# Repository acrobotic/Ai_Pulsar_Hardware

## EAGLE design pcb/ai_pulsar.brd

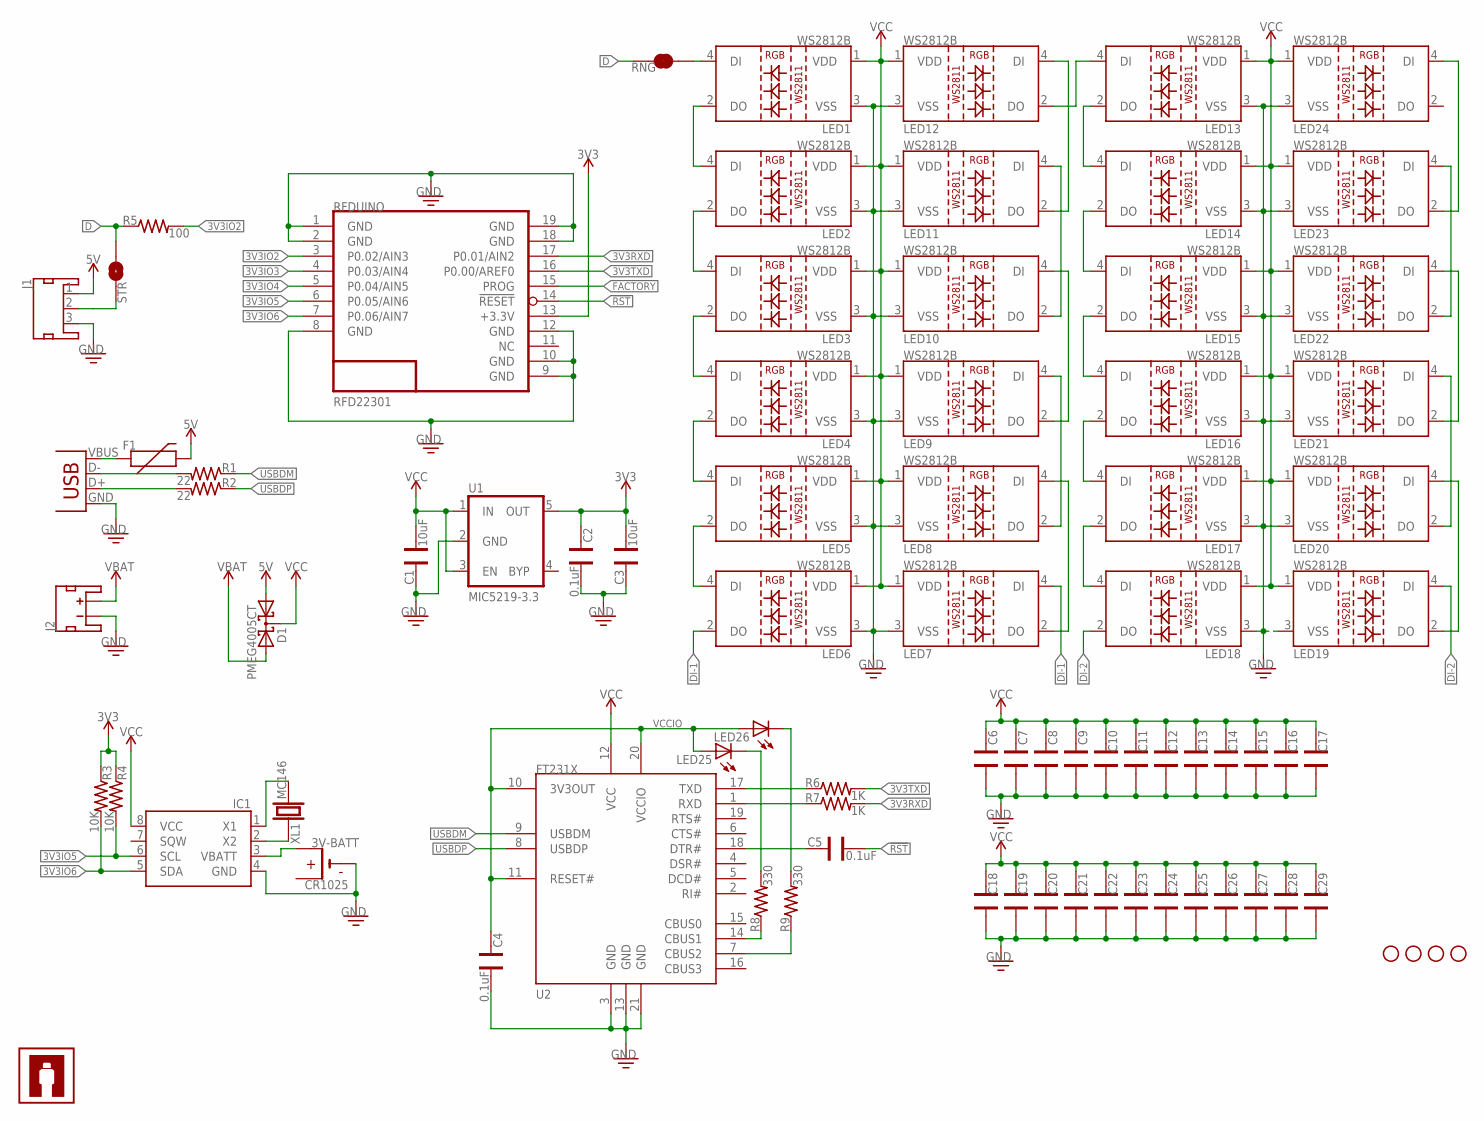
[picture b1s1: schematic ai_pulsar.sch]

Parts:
3V-BATT: CR1025; CR1025-SMD
C1, C3: 10uF; CAP-0603
C2, C4, C5: 0.1uF; CAP-0603
C6, C7, C8, C9, C10, C11, C12, C13, C14, C15, C16, C17, C18, C19, C20, C21, C22, C23, C24, C25, C26, C27, C28, C29: CAP0603; CAP-0603
D1: PMEG4005CT; SOT-23
F1: PTCSMD; PTC-1206
IC1: DS1307SO8-TIGHT; SO08-TIGHT
J1: JST-3P-MALE; JST-3P-SMD
J2: JST-2P-MALE; JST-2P-SMD
LED1, LED2, LED3, LED4, LED5, LED6, LED7, LED8, LED9, LED10, LED11, LED12, LED13, LED14, LED15, LED16, LED17, LED18, LED19, LED20, LED21, LED22, LED23, LED24: LED-WS2812B-SM
LED25, LED26: LED0603; LED-0603
R1, R2: 22; RES-0603
R3, R4: 10K; RES-0603
R5: 100; RES-0603
R6, R7: 1K; RES-0603
R8, R9: 330; RES-0603
RFDUINO: RFD22301
RNG: 1X02-SJ-NC
STANDOFF1, STANDOFF2, STANDOFF3, STANDOFF4: STAND-OFF4T; STAND-OFF-4T
STR: 1X02-SJ-NO
U1: MIC5219-3.3; SOT23-5
U2: FT231X-Q; QFN20
U$9: AI-LOGOXS; AI-LOGO-XS
USB1: USBMICROB-TH; USB-MICROB-TH
XL1: MC146; EPSON-MC146

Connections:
3V3: C2.2, C3.1, R3.1, R4.1, RFDUINO.13 (+3.3V), U1.5 (OUT)
3V3IO2: R5.2, RFDUINO.3 (P0.02/AIN3)
3V3IO3: RFDUINO.4 (P0.03/AIN4)
3V3IO4: RFDUINO.5 (P0.04/AIN5)
3V3IO5: IC1.6 (SCL), R4.2, RFDUINO.6 (P0.05/AIN6)
3V3IO6: IC1.5 (SDA), R3.2, RFDUINO.7 (P0.06/AIN7)
3V3RXD: R7.2, RFDUINO.17 (P0.01/AIN2)
3V3TXD: R6.2, RFDUINO.16 (P0.00/AREF0)
5V: D1.1 (A1), F1.2, J1.1
!RST: C5.1, RFDUINO.14 (!RESET)
D: J1.2, R5.1, RNG.2, STR.1
DI-1: LED6.2 (DO), LED7.4 (DI)
DI-2: LED18.2 (DO), LED19.4 (DI)
FACTORY: RFDUINO.15 (PROG)
GND: 3V-BATT.-, C1.2, C2.1, C3.2, C4.1, C6.1, C7.1, C8.1, C9.1, C10.1, C11.1, C12.1, C13.1, C14.1, C15.1, C16.1, C17.1, C18.1, C19.1, C20.1, C21.1, C22.1, C23.1, C24.1, C25.1, C26.1, C27.1, C28.1, C29.1, IC1.4 (GND), J1.3, J2.2 (-), LED1.3 (VSS), LED2.3 (VSS), LED3.3 (VSS), LED4.3 (VSS), LED5.3 (VSS), LED6.3 (VSS), LED7.3 (VSS), LED8.3 (VSS), LED9.3 (VSS), LED10.3 (VSS), LED11.3 (VSS), LED12.3 (VSS), LED13.3 (VSS), LED14.3 (VSS), LED15.3 (VSS), LED16.3 (VSS), LED17.3 (VSS), LED18.3 (VSS), LED19.3 (VSS), LED20.3 (VSS), LED21.3 (VSS), LED22.3 (VSS), LED23.3 (VSS), LED24.3 (VSS), RFDUINO.1 (GND), RFDUINO.2 (GND), RFDUINO.8 (GND), RFDUINO.9 (GND), RFDUINO.10 (GND), RFDUINO.12 (GND), RFDUINO.18 (GND), RFDUINO.19 (GND), U1.2 (GND), U2.3 (GND), U2.13 (GND), U2.21 (GND), USB1.GND
unnamed: 3V-BATT.+@1 (+1), 3V-BATT.+@2 (+1), IC1.3 (VBATT)
unnamed: R1.2, USB1.D-
unnamed: IC1.2 (X2), XL1.P$1 (1)
unnamed: IC1.1 (X1), XL1.P$2 (2)
unnamed: F1.1, USB1.VBUS
unnamed: R2.2, USB1.D+
unnamed: R7.1, U2.1 (RXD)
unnamed: R6.1, U2.17 (TXD)
unnamed: C5.2, U2.18 (DTR#)
unnamed: LED26.C, R9.2
unnamed: LED25.C, R8.2
unnamed: LED12.2 (DO), LED13.4 (DI)
unnamed: R8.1, U2.14 (CBUS1)
unnamed: R9.1, U2.7 (CBUS2)
unnamed: LED2.2 (DO), LED3.4 (DI)
unnamed: LED3.2 (DO), LED4.4 (DI)
unnamed: LED4.2 (DO), LED5.4 (DI)
unnamed: LED5.2 (DO), LED6.4 (DI)
unnamed: LED7.2 (DO), LED8.4 (DI)
unnamed: LED8.2 (DO), LED9.4 (DI)
unnamed: LED9.2 (DO), LED10.4 (DI)
unnamed: LED10.2 (DO), LED11.4 (DI)
unnamed: LED11.2 (DO), LED12.4 (DI)
unnamed: LED13.2 (DO), LED14.4 (DI)
unnamed: LED14.2 (DO), LED15.4 (DI)
unnamed: LED15.2 (DO), LED16.4 (DI)
unnamed: LED16.2 (DO), LED17.4 (DI)
unnamed: LED1.4 (DI), RNG.1
unnamed: LED1.2 (DO), LED2.4 (DI)
unnamed: LED17.2 (DO), LED18.4 (DI)
unnamed: LED19.2 (DO), LED20.4 (DI)
unnamed: LED20.2 (DO), LED21.4 (DI)
unnamed: LED21.2 (DO), LED22.4 (DI)
unnamed: LED22.2 (DO), LED23.4 (DI)
unnamed: LED23.2 (DO), LED24.4 (DI)
USBDM: R1.1, U2.9 (USBDM)
USBDP: R2.1, U2.8 (USBDP)
VBAT: D1.2 (A2), J2.1 (+)
VCC: C1.1, C6.2, C7.2, C8.2, C9.2, C10.2, C11.2, C12.2, C13.2, C14.2, C15.2, C16.2, C17.2, C18.2, C19.2, C20.2, C21.2, C22.2, C23.2, C24.2, C25.2, C26.2, C27.2, C28.2, C29.2, D1.3 (CC), IC1.8 (VCC), LED1.1 (VDD), LED2.1 (VDD), LED3.1 (VDD), LED4.1 (VDD), LED5.1 (VDD), LED6.1 (VDD), LED7.1 (VDD), LED8.1 (VDD), LED9.1 (VDD), LED10.1 (VDD), LED11.1 (VDD), LED12.1 (VDD), LED13.1 (VDD), LED14.1 (VDD), LED15.1 (VDD), LED16.1 (VDD), LED17.1 (VDD), LED18.1 (VDD), LED19.1 (VDD), LED20.1 (VDD), LED21.1 (VDD), LED22.1 (VDD), LED23.1 (VDD), LED24.1 (VDD), U1.1 (IN), U1.3 (EN), U2.12 (VCC)
VCCIO: C4.2, LED25.A, LED26.A, U2.10 (3V3OUT), U2.11 (RESET#), U2.20 (VCCIO)

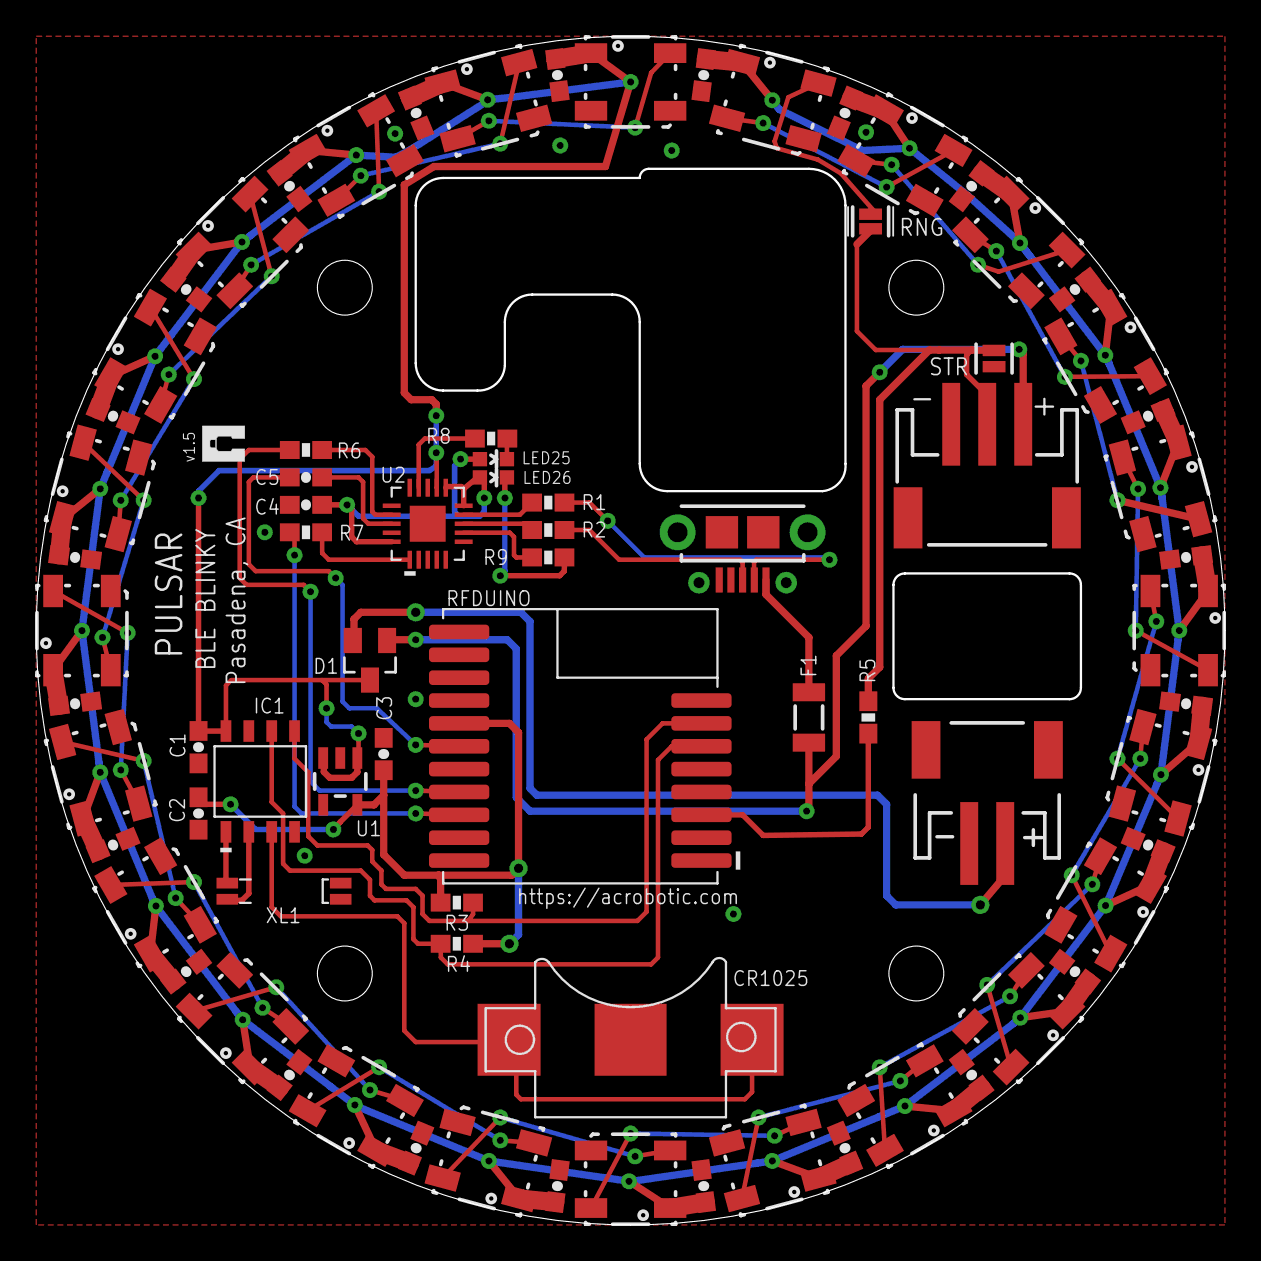
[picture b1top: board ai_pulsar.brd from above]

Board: 2 copper layers, 65.9 x 65.9 mm, 82 parts (0 on the bottom side), 52 nets.

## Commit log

2014-11-26 routing finished
2014-11-27 generated gerbers
2014-11-27 minor silkscreen changes
2014-12-17 renamed a few parts
2014-12-23 version 1.1. Fixed coin-cell polarity, added 5V on FTDI pins for easy programming
2014-12-23 added comment on remaining airwire.
2014-12-25 minor silkscreen fix
2015-05-26 Updating
2015-05-29 routing under way
2015-05-30 routed v1.3
2015-05-31 latest gerbers
2015-06-29 fiddling with cutouts
2015-07-20 bigger cutout for micro-B connector
